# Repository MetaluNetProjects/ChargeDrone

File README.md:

# ChargeDrone
Charger for 2-li_Ion-18650-batteries pack.

## exported files:

CHARGEDRONE-v1.zip : PCB manufacturer files

ChargeDronePCB-v1.xls : Bill of Materials

ChargeDrone-schema.pdf : schematic

ChargeDroneWRL-v1.zip : 3D export

PlexiCutting/ : directory containing plexiglas cutting files

### metalu.net 2020 for GroupeF

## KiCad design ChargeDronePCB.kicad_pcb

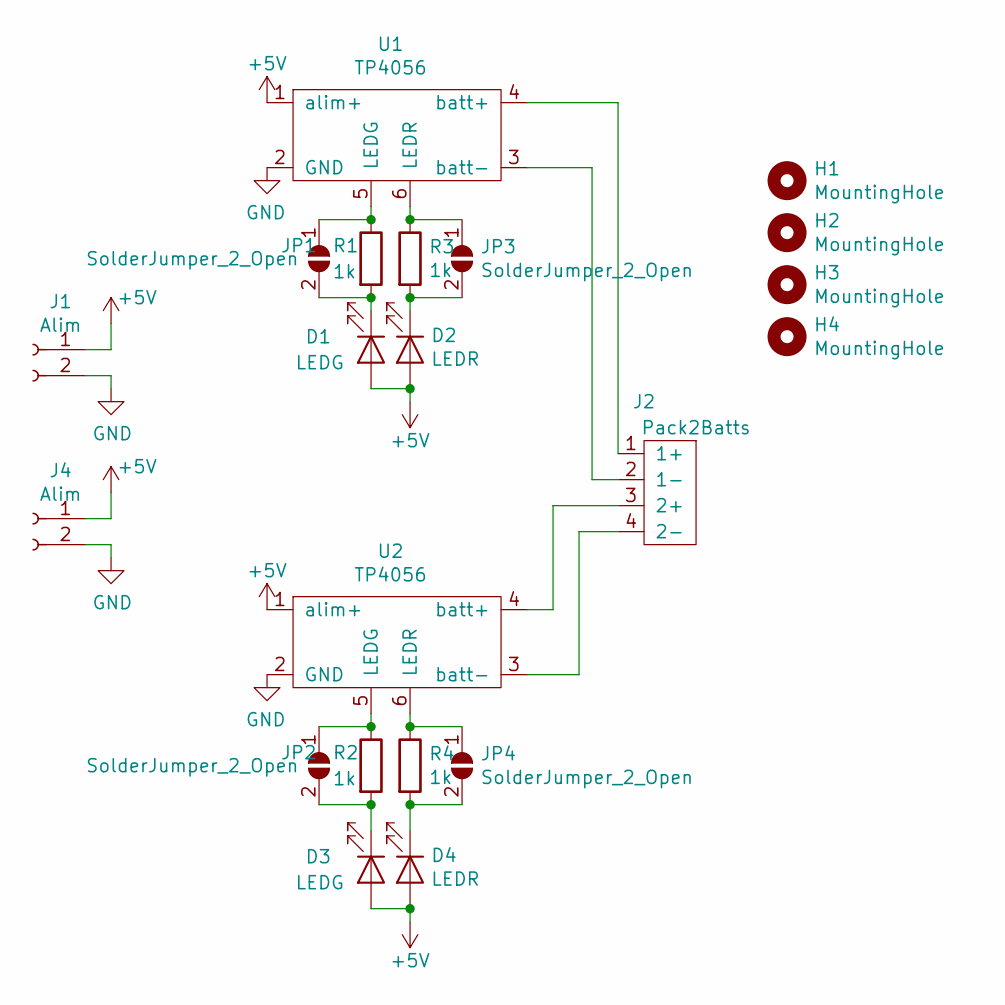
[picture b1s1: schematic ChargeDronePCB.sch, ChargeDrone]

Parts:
D1, D3: LEDG; LED_D3.0mm
D2, D4: LEDR; LED_D3.0mm
H1, H2, H3, H4: MountingHole; MountingHole_3.2mm_M3_DIN965_Pad
J1, J4: Alim; TerminalBlock_bornier-2_P5.08mm
J2: Pack2Batts; PackBatt
JP1, JP2, JP3, JP4: SolderJumper_2_Open; GS2
R1, R2, R3, R4: 1k; R_Axial_DIN0207_L6.3mm_D2.5mm_P7.62mm_Horizontal
U1, U2: TP4056

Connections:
+5V: D1.2 (A), D2.2 (A), D3.2 (A), D4.2 (A), J1.1, J4.1, U1.1 (alim+), U2.1 (alim+)
GND: J1.2, J4.2, U1.2 (GND), U2.2 (GND)
unnamed: D1.1 (K), JP1.2 (B), R1.2
unnamed: D2.1 (K), JP3.2 (B), R3.2
unnamed: D3.1 (K), JP2.2 (B), R2.2
unnamed: D4.1 (K), JP4.2 (B), R4.2
unnamed: J2.1 (1+), U1.4 (batt+)
unnamed: J2.2 (1-), U1.3 (batt-)
unnamed: J2.3 (2+), U2.4 (batt+)
unnamed: J2.4 (2-), U2.3 (batt-)
unnamed: JP1.1 (A), R1.1, U1.5 (LEDG)
unnamed: JP2.1 (A), R2.1, U2.5 (LEDG)
unnamed: JP3.1 (A), R3.1, U1.6 (LEDR)
unnamed: JP4.1 (A), R4.1, U2.6 (LEDR)

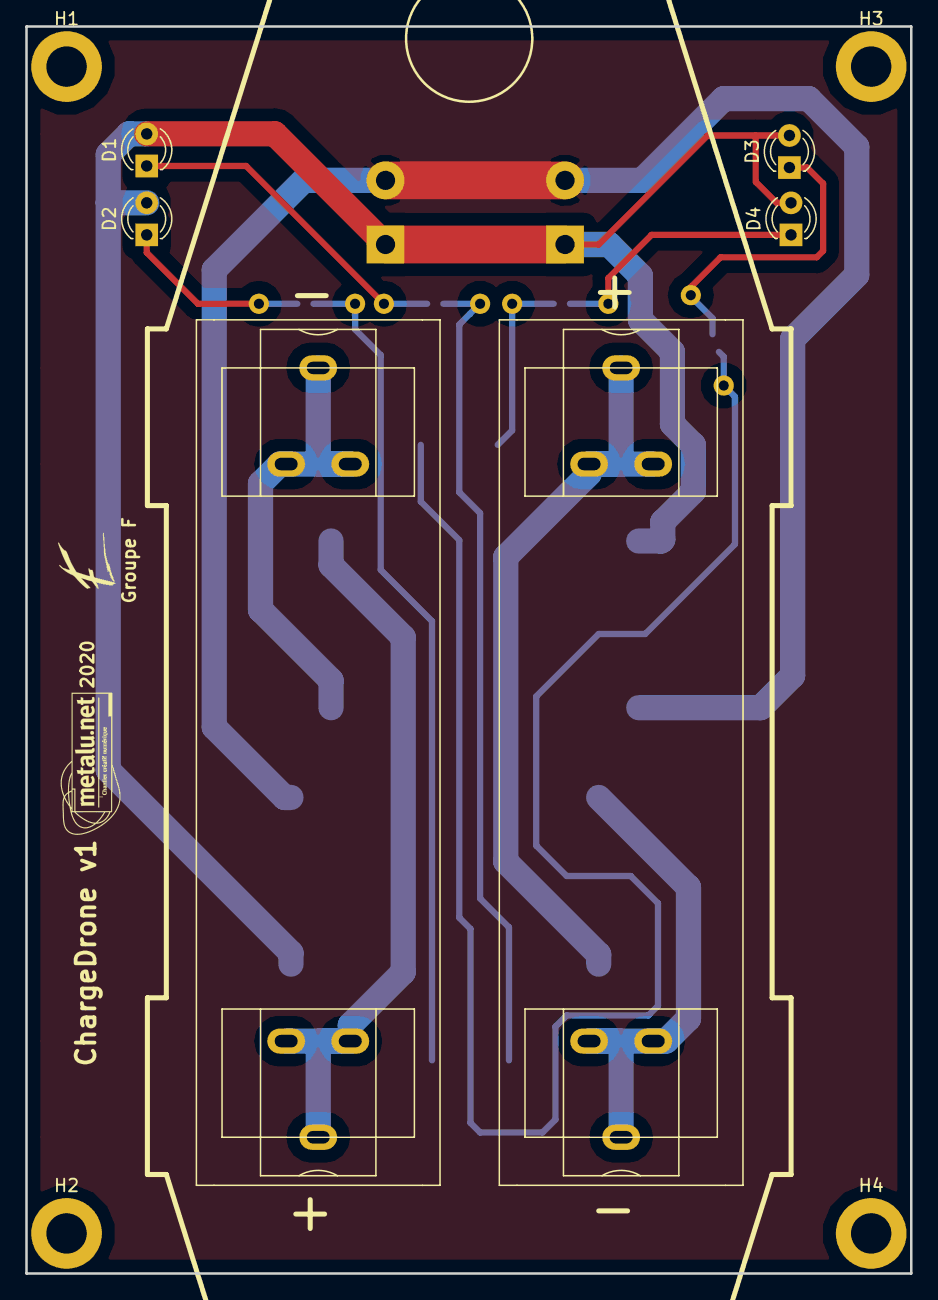
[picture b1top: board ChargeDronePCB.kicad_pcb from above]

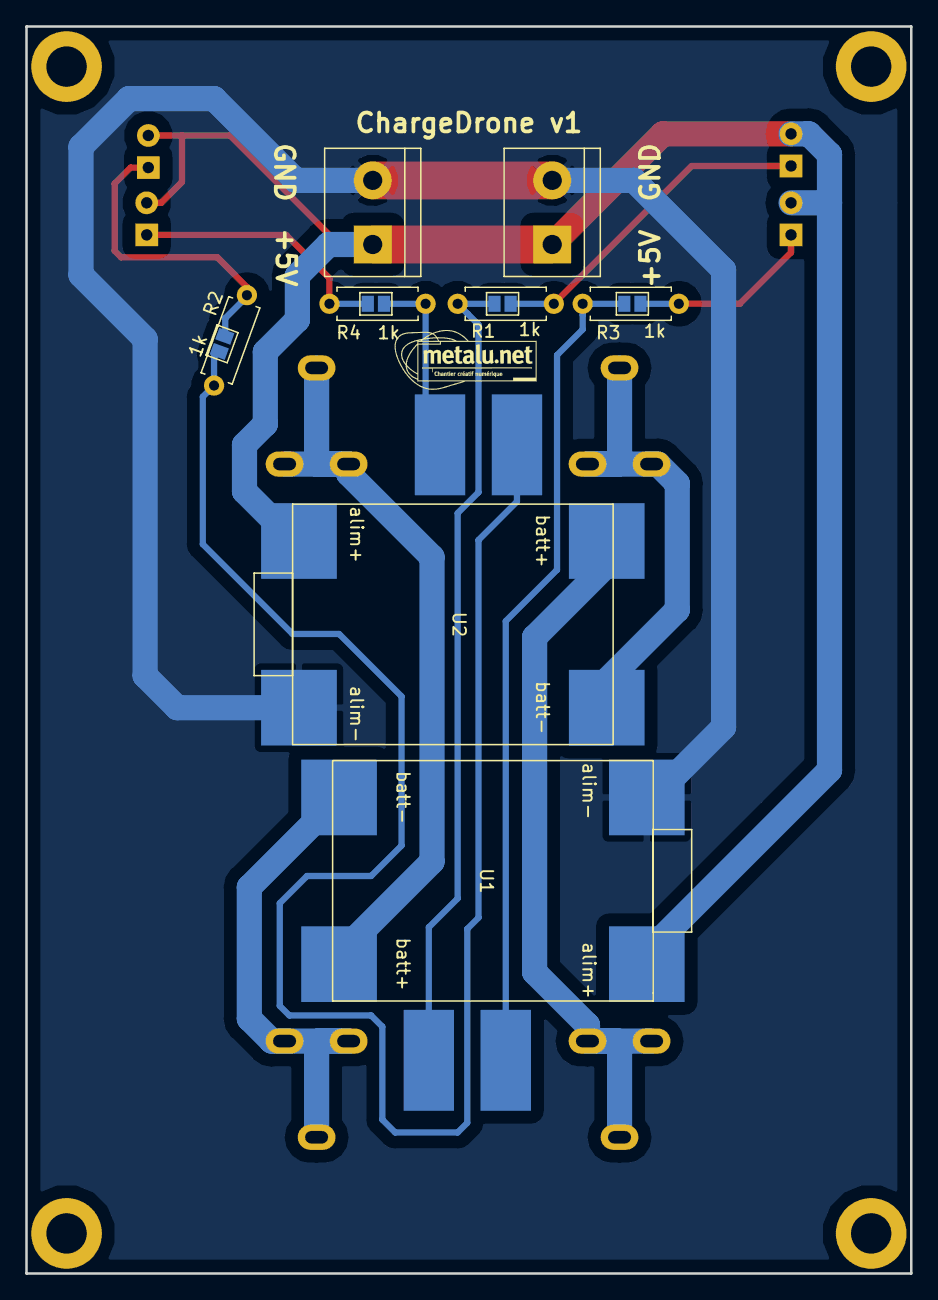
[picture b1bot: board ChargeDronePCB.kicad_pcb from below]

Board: 2 copper layers, 70.1 x 98.8 mm, 21 parts (12 on the bottom side), 14 nets.

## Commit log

2020-12-16 add ChargeDrone-schema.pdf
2020-12-16 add BOM as xls, and update README
2020-12-16 add plexi cutting files
